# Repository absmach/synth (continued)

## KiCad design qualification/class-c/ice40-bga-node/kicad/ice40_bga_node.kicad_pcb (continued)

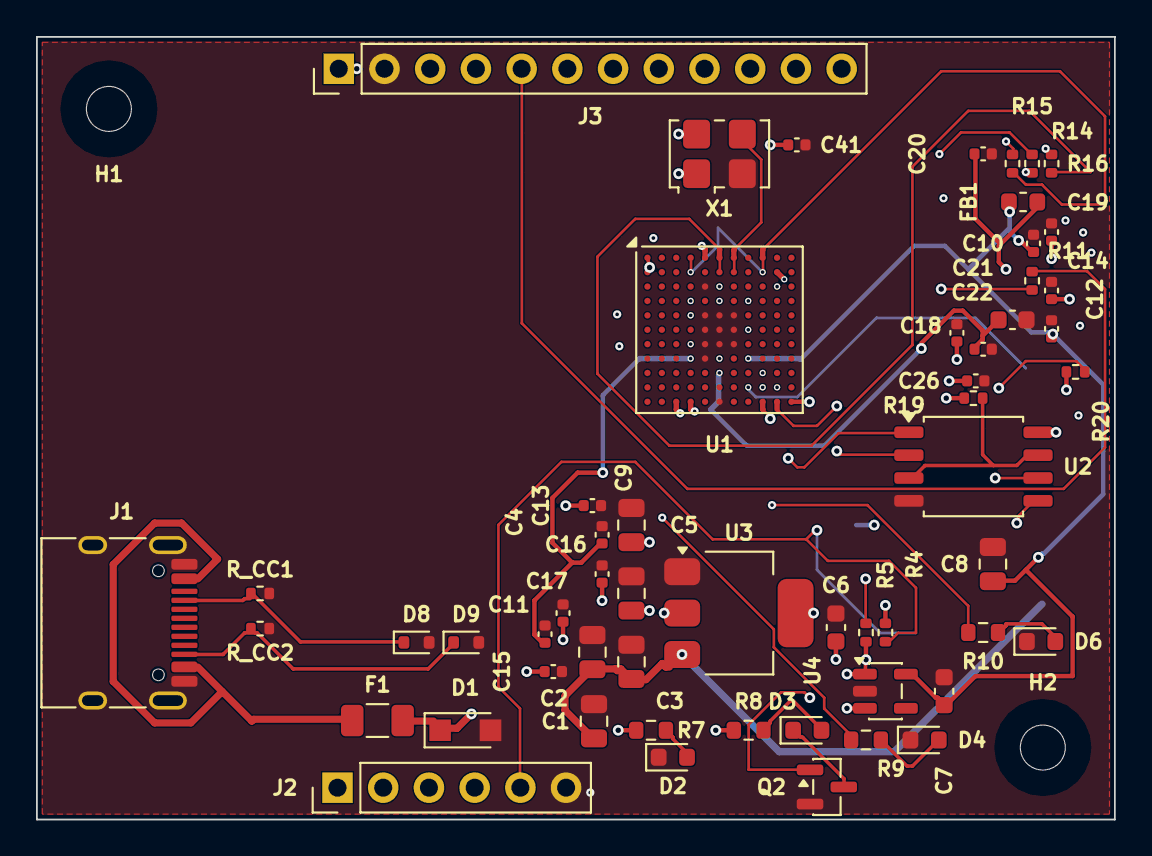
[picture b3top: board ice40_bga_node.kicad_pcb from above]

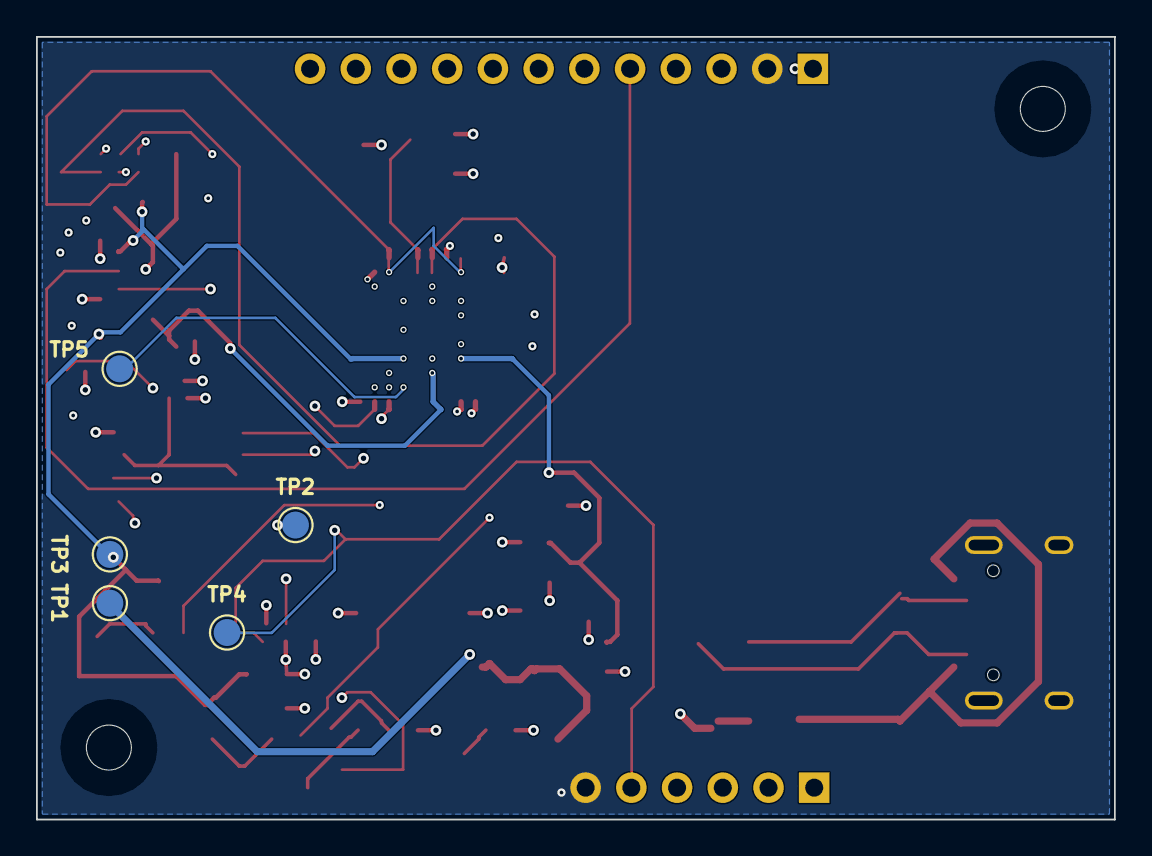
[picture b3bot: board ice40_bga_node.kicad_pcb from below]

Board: 6 copper layers, 59.9 x 43.5 mm, 63 parts (5 on the bottom side), 31 nets.

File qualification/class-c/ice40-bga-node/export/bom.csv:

refdes,value,kind,description,kicad_symbol,kicad_footprint,lcsc_pn,mpn
C1,10uF,capacitor,"Generic 0805 MLCC, X7R/X5R, any value",Device:C,Capacitor_SMD:C_0805_2012Metric,,
C10,100nF,capacitor,"Generic 0402 MLCC, X7R/X5R, any value",Device:C,Capacitor_SMD:C_0402_1005Metric,,
C11,100nF,capacitor,"Generic 0402 MLCC, X7R/X5R, any value",Device:C,Capacitor_SMD:C_0402_1005Metric,,
C12,100nF,capacitor,"Generic 0402 MLCC, X7R/X5R, any value",Device:C,Capacitor_SMD:C_0402_1005Metric,,
C13,100nF,capacitor,"Generic 0402 MLCC, X7R/X5R, any value",Device:C,Capacitor_SMD:C_0402_1005Metric,,
C14,100nF,capacitor,"Generic 0402 MLCC, X7R/X5R, any value",Device:C,Capacitor_SMD:C_0402_1005Metric,,
C15,100nF,capacitor,"Generic 0402 MLCC, X7R/X5R, any value",Device:C,Capacitor_SMD:C_0402_1005Metric,,
C16,100nF,capacitor,"Generic 0402 MLCC, X7R/X5R, any value",Device:C,Capacitor_SMD:C_0402_1005Metric,,
C17,100nF,capacitor,"Generic 0402 MLCC, X7R/X5R, any value",Device:C,Capacitor_SMD:C_0402_1005Metric,,
C18,100nF,capacitor,"Generic 0402 MLCC, X7R/X5R, any value",Device:C,Capacitor_SMD:C_0402_1005Metric,,
C19,100nF,capacitor,"Generic 0402 MLCC, X7R/X5R, any value",Device:C,Capacitor_SMD:C_0402_1005Metric,,
C2,10uF,capacitor,"Generic 0805 MLCC, X7R/X5R, any value",Device:C,Capacitor_SMD:C_0805_2012Metric,,
C20,100nF,capacitor,"Generic 0402 MLCC, X7R/X5R, any value",Device:C,Capacitor_SMD:C_0402_1005Metric,,
C21,100nF,capacitor,"Generic 0402 MLCC, X7R/X5R, any value",Device:C,Capacitor_SMD:C_0402_1005Metric,,
C22,1uF,capacitor,"Generic 0603 MLCC, X7R/X5R, any value",Device:C,Capacitor_SMD:C_0603_1608Metric,,
C26,100nF,capacitor,"Generic 0402 MLCC, X7R/X5R, any value",Device:C,Capacitor_SMD:C_0402_1005Metric,,
C3,10uF,capacitor,"Generic 0805 MLCC, X7R/X5R, any value",Device:C,Capacitor_SMD:C_0805_2012Metric,,
C4,10uF,capacitor,"Generic 0805 MLCC, X7R/X5R, any value",Device:C,Capacitor_SMD:C_0805_2012Metric,,
C5,10uF,capacitor,"Generic 0805 MLCC, X7R/X5R, any value",Device:C,Capacitor_SMD:C_0805_2012Metric,,
C6,1uF,capacitor,"Generic 0603 MLCC, X7R/X5R, any value",Device:C,Capacitor_SMD:C_0603_1608Metric,,
C7,1uF,capacitor,"Generic 0603 MLCC, X7R/X5R, any value",Device:C,Capacitor_SMD:C_0603_1608Metric,,
C8,4.7uF,capacitor,"Generic 0805 MLCC, X7R/X5R, any value",Device:C,Capacitor_SMD:C_0805_2012Metric,,
C9,100nF,capacitor,"Generic 0402 MLCC, X7R/X5R, any value",Device:C,Capacitor_SMD:C_0402_1005Metric,,
D1,PTVS6V0S1UR,diode,"Nexperia PTVS6V0S1UR 400 W unidirectional TVS, 6.0 V standoff, SOD123W, for VBUS and CC",Device:D_Zener,Diode_SMD:Nexperia_CFP3_SOD-123W,,PTVS6V0S1UR
D2,0603-GREEN,led,"Green LED, 0603 package, ~2.2V Vf",Device:LED,LED_SMD:LED_0603_1608Metric,C72043,0603-GREEN
D3,(no value),led,"Amber surface-mount LED, 0603",Device:LED,LED_SMD:LED_0603_1608Metric,,
D4,0603-RED,led,"Red LED, 0603 package, ~2.0V Vf",Device:LED,LED_SMD:LED_0603_1608Metric,C2286,0603-RED
D6,0603-RED,led,"Red LED, 0603 package, ~2.0V Vf",Device:LED,LED_SMD:LED_0603_1608Metric,C2286,0603-RED
F1,MF-NSMF050-2,fuse,"Bourns MF-NSMF050-2 resettable fuse, 0.5 A hold, 13.2 V, 1206",Device:Polyfuse,Fuse:Fuse_1206_3216Metric,C75464,MF-NSMF050-2
FB1,(no value),inductor,"0603 ferrite bead, 600Ω @ 100MHz — EMI suppression",Device:FerriteBead,Inductor_SMD:L_0603_1608Metric,,
H1,(no value),mounting_hole,M2.5 non-plated mounting hole (NPTH) for a board corner,Mechanical:MountingHole,MountingHole:MountingHole_2.5mm,,
H2,(no value),mounting_hole,M2.5 non-plated mounting hole (NPTH) for a board corner,Mechanical:MountingHole,MountingHole:MountingHole_2.5mm,,
J1,HX PZ2.54-1x2P ZZ,connector,"1x2 through-hole pin header, 2.54mm pitch, for a jumper",Connector_Generic:Conn_01x02,Connector_PinHeader_2.54mm:PinHeader_1x02_P2.54mm_Vertical,C32713268,HX PZ2.54-1x2P ZZ
J3,(no value),connector,"1x12 through-hole pin header, 2.54 mm pitch (GPIO); datasheet_url is the product page of the Harwin M20 series, no manufacturer PDF link was verifiable",Connector_Generic:Conn_01x12,Connector_PinHeader_2.54mm:PinHeader_1x12_P2.54mm_Vertical,,
Q1,SI2301CDS-T1-GE3,transistor,"Vishay Si2301 P-channel power MOSFET, SOT-23",Transistor_FET:Si2301CDS,Package_TO_SOT_SMD:SOT-23,C10487,SI2301CDS-T1-GE3
R10,1k,resistor,"Generic 0603 thick-film resistor, any value",Device:R_US,Resistor_SMD:R_0603_1608Metric,,
R11,100,resistor,"Generic 0402 thick-film resistor, any value",Device:R_US,Resistor_SMD:R_0402_1005Metric,,
R14,100,resistor,"Generic 0402 thick-film resistor, any value",Device:R_US,Resistor_SMD:R_0402_1005Metric,,
R15,100,resistor,"Generic 0402 thick-film resistor, any value",Device:R_US,Resistor_SMD:R_0402_1005Metric,,
R16,100,resistor,"Generic 0402 thick-film resistor, any value",Device:R_US,Resistor_SMD:R_0402_1005Metric,,
R19,10k,resistor,"Generic 0402 thick-film resistor, any value",Device:R_US,Resistor_SMD:R_0402_1005Metric,,
R20,10k,resistor,"Generic 0402 thick-film resistor, any value",Device:R_US,Resistor_SMD:R_0402_1005Metric,,
R3,100k,resistor,"Generic 0603 thick-film resistor, any value",Device:R_US,Resistor_SMD:R_0603_1608Metric,,
R4,10k,resistor,"Generic 0402 thick-film resistor, any value",Device:R_US,Resistor_SMD:R_0402_1005Metric,,
R5,10k,resistor,"Generic 0402 thick-film resistor, any value",Device:R_US,Resistor_SMD:R_0402_1005Metric,,
R7,1k,resistor,"Generic 0603 thick-film resistor, any value",Device:R_US,Resistor_SMD:R_0603_1608Metric,,
R8,1k,resistor,"Generic 0603 thick-film resistor, any value",Device:R_US,Resistor_SMD:R_0603_1608Metric,,
R9,1k,resistor,"Generic 0603 thick-film resistor, any value",Device:R_US,Resistor_SMD:R_0603_1608Metric,,
TP1,(no value),testpoint,"SMD test point pad, 1.5 mm — probe point for a net",Connector:TestPoint,TestPoint:TestPoint_Pad_D1.5mm,,
TP2,(no value),testpoint,"SMD test point pad, 1.5 mm — probe point for a net",Connector:TestPoint,TestPoint:TestPoint_Pad_D1.5mm,,
TP3,(no value),testpoint,"SMD test point pad, 1.5 mm — probe point for a net",Connector:TestPoint,TestPoint:TestPoint_Pad_D1.5mm,,
TP4,(no value),testpoint,"SMD test point pad, 1.5 mm — probe point for a net",Connector:TestPoint,TestPoint:TestPoint_Pad_D1.5mm,,
TP5,(no value),testpoint,"SMD test point pad, 1.5 mm — probe point for a net",Connector:TestPoint,TestPoint:TestPoint_Pad_D1.5mm,,
U1,ICE40HX4K-BG121,fpga,"Lattice iCE40 HX4K FPGA, 121-ball 0.8mm BGA. Copy of registry part ice40hx4k_bg121 with exactly one change: vpp_fast (B10) is a passive pin that is not required, so it can be left unconnected.",FPGA_Lattice:ICE40HX4K-BG121,Package_BGA:BGA-121_9.0x9.0mm_Layout11x11_P0.8mm_Ball0.4mm_Pad0.35mm_NSMD,,ICE40HX4K-BG121
U2,W25Q128JVSIQ,memory,"Winbond W25Q128JVSIQ 128Mbit SPI NOR flash, SOIC-8 208 mil (5.3 mm body, 7.7 mm lead span, 1.27 mm pitch)",Memory_Flash:W25Q128JVS,Package_SO:SOIC-8_5.3x5.3mm_P1.27mm,C97521,W25Q128JVSIQ
U3,AMS1117-3.3,regulator,"AMS1117-3.3 fixed 3.3V LDO regulator, SOT-223 — common JLC stock",Regulator_Linear:AMS1117-3.3,Package_TO_SOT_SMD:SOT-223-3_TabPin2,C6186,AMS1117-3.3
U4,TLV70012-1.2,regulator,"TI TLV70012 1.2 V fixed LDO, 200 mA, 2.0 to 5.5 V input, SOT-23-THIN (DDC, TSOT-23-5). Pinout 1 IN, 2 GND, 3 EN, 4 NC, 5 OUT per TI TLV700xx datasheet SLVSA00; 1 uF input and output capacitors.",Regulator_Linear:TLV70012_SOT23-5,Package_TO_SOT_SMD:TSOT-23-5,,TLV70012DDCR
